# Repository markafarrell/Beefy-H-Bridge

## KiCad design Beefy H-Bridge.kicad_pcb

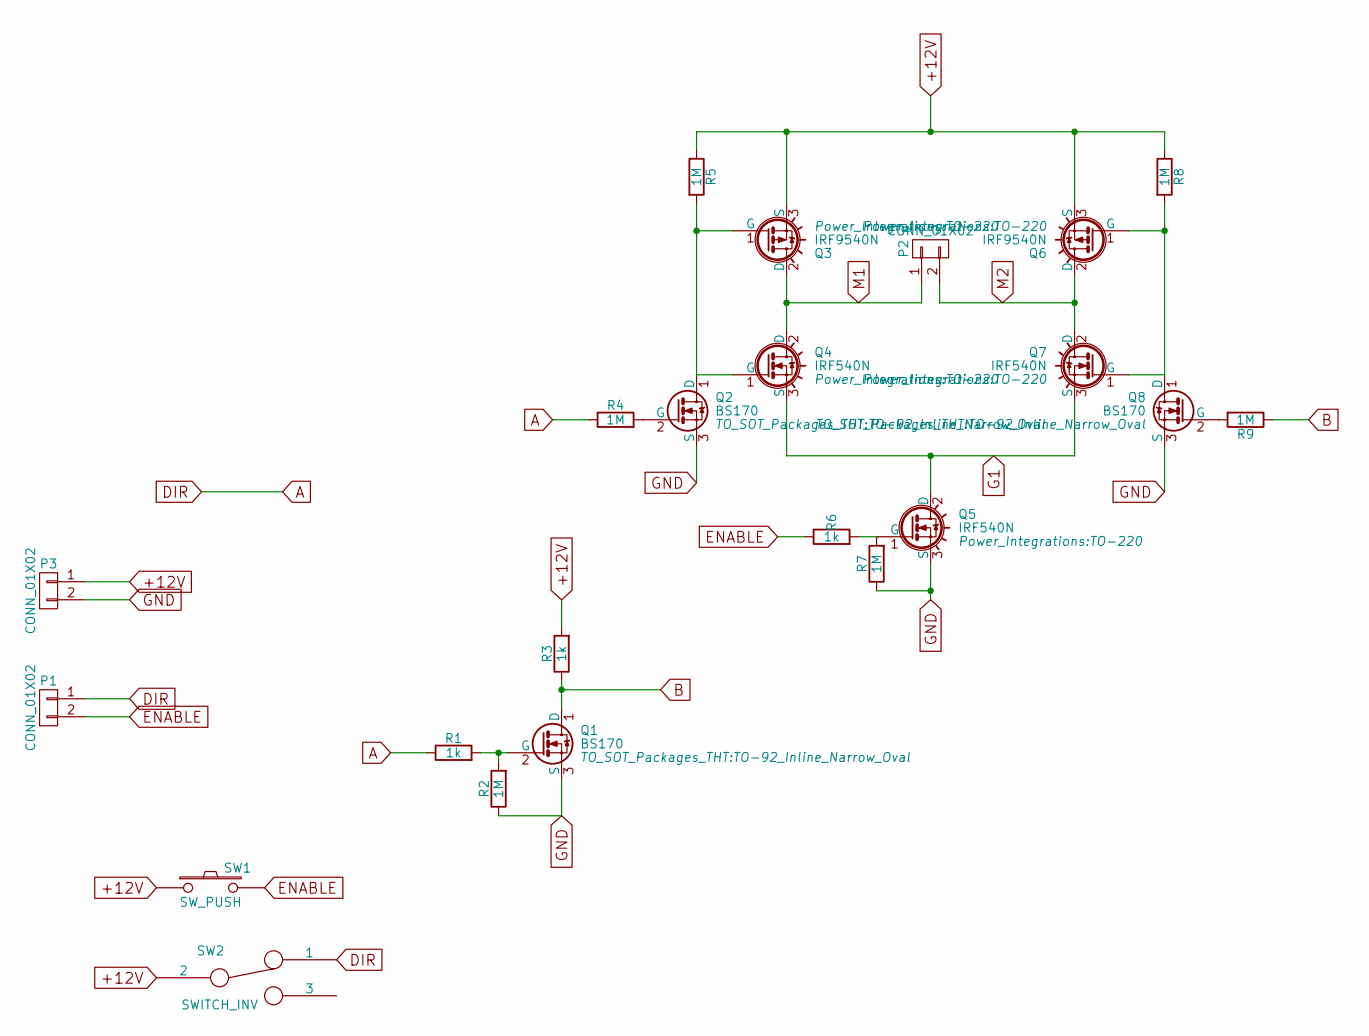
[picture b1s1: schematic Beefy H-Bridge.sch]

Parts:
P1, P2, P3: CONN_01X02; TerminalBlock_Pheonix_MKDS1.5-2pol
Q1, Q2, Q8: BS170; TO-92_Inline_Narrow_Oval
Q3, Q6: IRF9540N; TO-220
Q4, Q5, Q7: IRF540N; TO-220
R1, R3, R6: 1k; Resistor_Vertical_RM5mm
R2, R4, R5, R7, R8, R9: 1M; Resistor_Vertical_RM5mm
SW1: SW_PUSH; SW_PUSH_SMALL
SW2: SWITCH_INV; SW_Micro_SPST

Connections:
+12V: P3.1, Q3.3 (S), Q6.3 (S), R3.2, R5.1, R8.1, SW1.1, SW2.2
A: P1.1, R1.1, R4.1, SW2.1
B: Q1.1 (D), R3.1, R9.1
ENABLE: P1.2, R6.1, SW1.2
G1: Q4.3 (S), Q5.2 (D), Q7.3 (S)
GND: P3.2, Q1.3 (S), Q2.3 (S), Q5.3 (S), Q8.3 (S), R2.1, R7.1
M1: P2.1, Q3.2 (D), Q4.2 (D)
M2: P2.2, Q6.2 (D), Q7.2 (D)
unnamed: Q1.2 (G), R1.2, R2.2
unnamed: Q2.1 (D), Q3.1 (G), Q4.1 (G), R5.2
unnamed: Q2.2 (G), R4.2
unnamed: Q5.1 (G), R6.2, R7.2
unnamed: Q6.1 (G), Q7.1 (G), Q8.1 (D), R8.2
unnamed: Q8.2 (G), R9.2

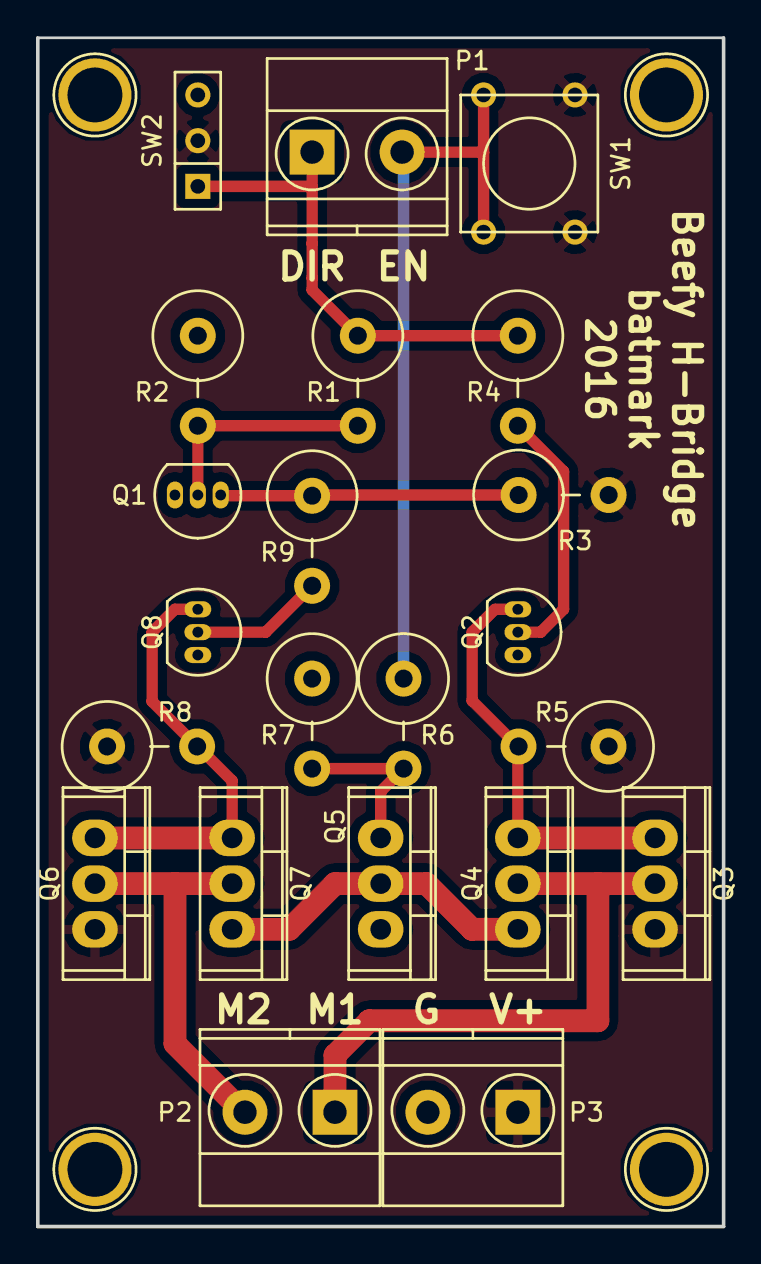
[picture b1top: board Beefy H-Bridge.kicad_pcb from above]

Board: 2 copper layers, 38.1 x 66.0 mm, 22 parts (0 on the bottom side), 14 nets.

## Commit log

2016-07-03 :confetti_ball: Added .gitattributes & .gitignore files
